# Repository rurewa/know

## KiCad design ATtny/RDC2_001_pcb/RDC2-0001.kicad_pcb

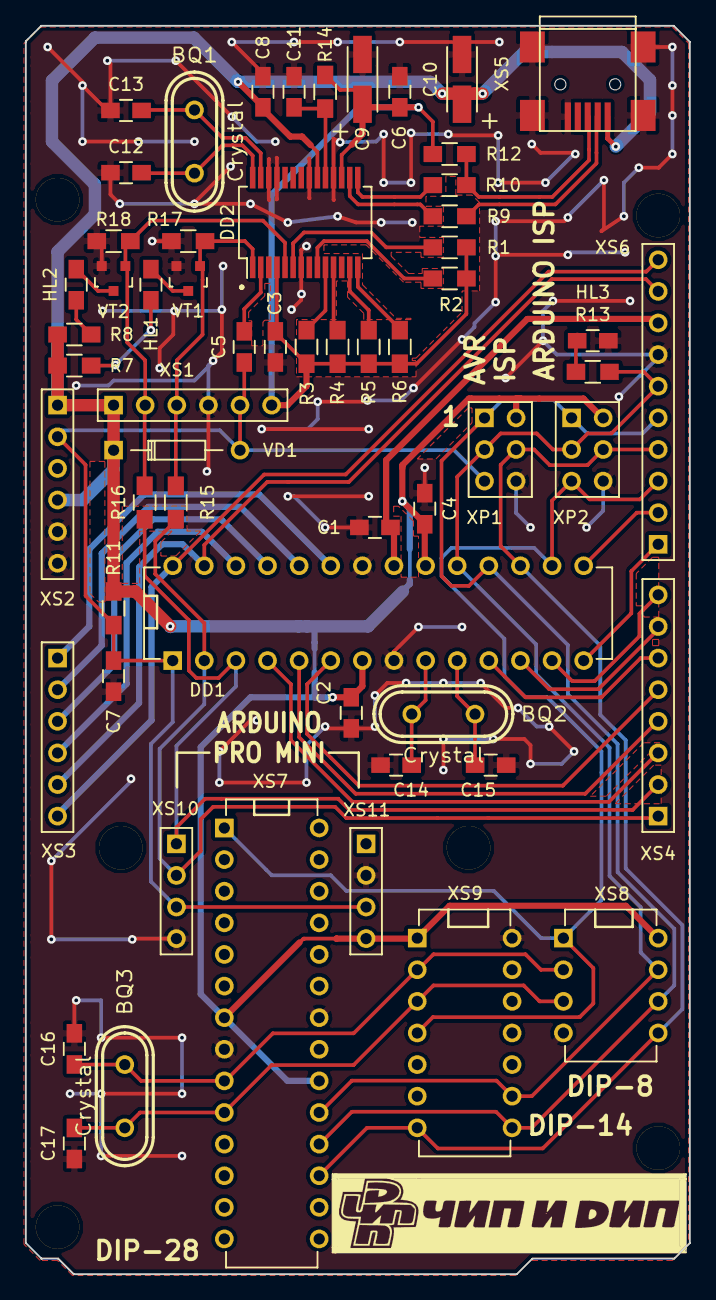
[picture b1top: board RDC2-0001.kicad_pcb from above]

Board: 2 copper layers, 53.3 x 100.3 mm, 59 parts (0 on the bottom side), 50 nets.

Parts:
BQ1, BQ2, BQ3: Crystal; CRYST_hc-49u_mm
C1, C2, C3, C4, C5, C6, C7, C8, C11, C12, C13, C14, C15, C16, C17: C; C_0805_HandSoldering
C9, C10: CP; TantalC_SizeA_EIA-3216_HandSoldering_mm
DD1: ATMEGA328P-P; DIP-28_W7.62mm_0.9x1.5
DD2: PL2303TA; SSOP-28_5.3x10.2mm_Pitch0.65mm
HL1, HL2, HL3: LED; C_0805_HandSoldering
R1, R2, R3, R4, R5, R6, R7, R8, R9, R10, R11, R12, R13, R14, R15, R16, R17, R18: R; R_0805_HandSoldering
VD1: D; Diode_DO-35_SOD27_Horizontal_RM10_mm
VT1, VT2: BSS138; SOT-23_mm
XP1, XP2: CONN_02X03; Pin_Header_Straight_2x03_mm
XS1, XS2, XS3: CONN_01X06; Pin_Header_Straight_1x06_mm
XS4: CONN_01X08; Pin_Header_Straight_1x08_mm
XS5: USB_OTG; USB_Mini-B_mm
XS6: CONN_01X10; Pin_Header_Straight_1x10_mm
XS7: ATMEGA328P-P; DIP-28_W7.62mm_0.9x1.5
XS8: ATTINY13A-P; DIP-8_W7.62mm_0.9x1.5
XS9: ATTINY24A-P; DIP-14_W7.62mm_0.9x1.5
XS10, XS11: CONN_01X04; Pin_Header_Straight_1x04_mm

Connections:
3V3: C3.2, C6.1, C9.1, DD2.4, DD2.17, R1.1, R2.1, R3.1, R4.1, R5.1, R6.1, R12.2, R14.2, XS1.6
5V: C2.1, C4.1, C8.1, C10.1, DD1.7, DD1.20, DD2.20, R7.1, R8.1, R11.1, VD1.1, XP1.2, XP2.2, XS1.1, XS2.1, XS2.4, XS5.1, XS7.7, XS7.20, XS8.8, XS9.1, XS11.4
A0: DD1.23, XS3.1
A1: DD1.24, XS3.2
A2: DD1.25, XS3.3
A3: DD1.26, XS3.4
A4/SDA: DD1.27, XS3.5, XS6.9
A5/SCL: DD1.28, XS3.6, XS6.10
AREF: C1.1, DD1.21, XS6.8
D0: DD1.2, R15.1, XS4.1, XS10.2
D1: DD1.3, R16.1, XS4.2, XS10.1
D2: DD1.4, XS4.3
D3: DD1.5, XS4.4
D4: DD1.6, XS4.5
D5: DD1.11, XS4.6
D6: DD1.12, XS4.7
D7: DD1.13, XS4.8
D8: DD1.14, XS6.1
D9: DD1.15, XS6.2
D10/SS: DD1.16, XP2.5, XS6.3, XS7.1, XS8.1, XS9.4
D11/MOSI: DD1.17, XP1.4, XP2.4, XS6.4, XS7.17, XS8.5, XS9.7
D12/MISO: DD1.18, XP1.1, XP2.1, XS6.5, XS7.18, XS8.6, XS9.8
D13/SCK: DD1.19, R13.1, XP1.3, XP2.3, XS6.6, XS7.19, XS8.7, XS9.9
GND: C1.2, C2.2, C3.1, C4.2, C6.2, C7.2, C8.2, C9.2, C10.2, C11.2, C12.1, C13.1, C14.1, C15.1, C16.1, C17.1, DD1.8, DD1.22, DD2.7, DD2.18, DD2.21, DD2.25, DD2.26, HL3.1, R17.2, R18.2, VT1.2, VT2.2, XP1.6, XP2.6, XS1.4, XS2.5, XS2.6, XS5.5, XS5.6, XS6.7, XS7.8, XS7.22, XS8.4, XS9.14, XS10.4, XS11.2
unnamed: BQ1.1, C12.2, DD2.28
unnamed: BQ1.2, C13.2, DD2.27
unnamed: BQ2.1, C14.2, DD1.9
unnamed: BQ2.2, C15.2, DD1.10
unnamed: C5.1, DD2.2
unnamed: C11.1, DD2.19, R14.1
unnamed: DD2.6, R1.2
unnamed: DD2.9, R2.2
unnamed: DD2.10, R3.2
unnamed: DD2.11, R4.2
unnamed: DD2.13, R5.2
unnamed: DD2.14, R6.2
unnamed: DD2.15, R10.1
unnamed: DD2.16, R9.1
unnamed: HL1.1, VT1.3
unnamed: HL1.2, R7.2
unnamed: HL2.1, VT2.3
unnamed: HL2.2, R8.2
unnamed: HL3.2, R13.2
unnamed: R9.2, XS5.2
unnamed: R10.2, R12.1, XS5.3
RES: C5.2, C7.1, DD1.1, R11.2, VD1.2, XP1.5, XS1.5, XS2.2, XS10.3, XS11.3
RXD: DD2.5, R16.2, R18.1, VT2.1, XS1.2
TXD: DD2.1, R15.2, R17.1, VT1.1, XS1.3
XTAL1: BQ3.1, C16.2, XS7.9, XS8.2, XS9.2
XTAL2: BQ3.2, C17.2, XS7.10, XS8.3, XS9.3

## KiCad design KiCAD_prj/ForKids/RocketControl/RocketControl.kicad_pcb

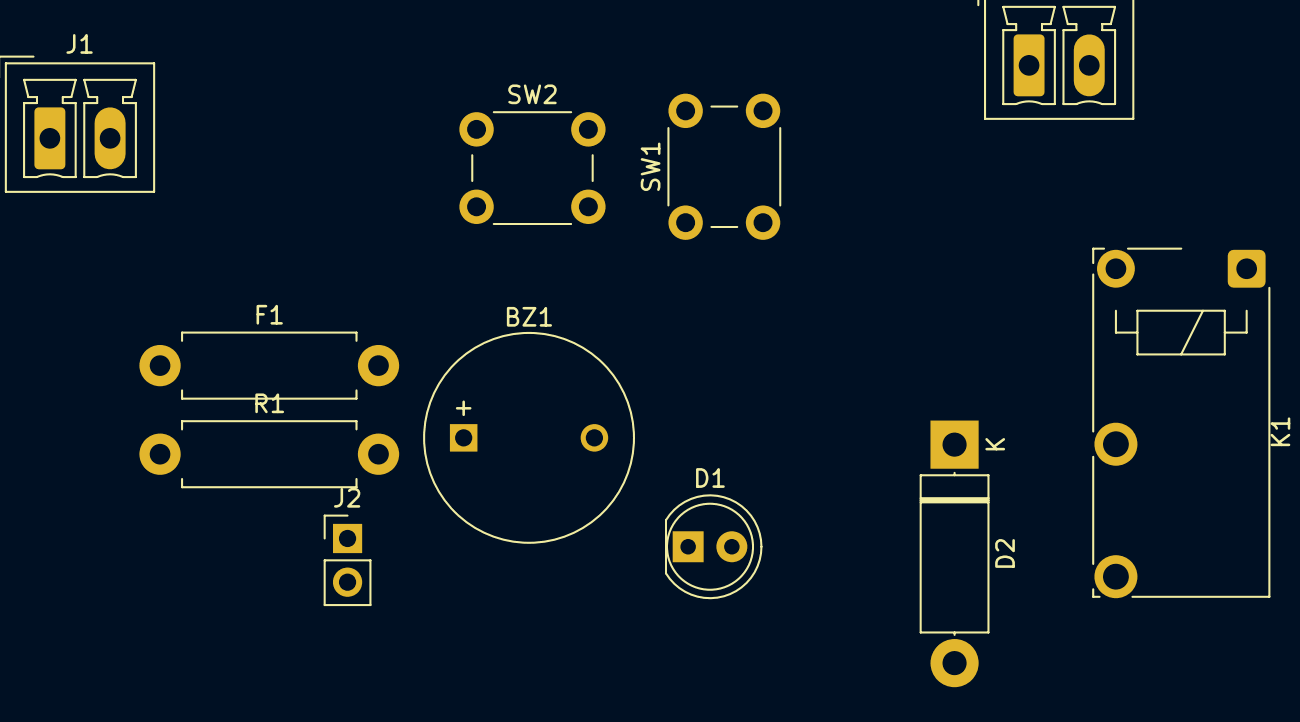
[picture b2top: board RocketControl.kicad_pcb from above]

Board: 2 copper layers, 11 parts (0 on the bottom side), 7 nets, no tracks yet.

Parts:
BZ1: Buzzer; MagneticBuzzer_ProSignal_ABI-010-RC
D1: LED; LED_D5.0mm
D2: DIODE; D_5W_P12.70mm_Horizontal
F1: 5A; R_Axial_DIN0411_L9.9mm_D3.6mm_P12.70mm_Horizontal
J1: Conn_01x02_Female; PhoenixContact_MCV_1,5_2-G-3.5_1x02_P3.50mm_Vertical
J2: Screw_Terminal_01x02; PinHeader_1x02_P2.54mm_Vertical
K1: DIPxx-1Axx-11x; Relay_SPST_TE_PCH-1xxx2M
L1: L; PhoenixContact_MCV_1,5_2-G-3.5_1x02_P3.50mm_Vertical
R1: 10K; R_Axial_DIN0411_L9.9mm_D3.6mm_P12.70mm_Horizontal
SW1, SW2: SW_MEC_5G; SW_PUSH_6mm

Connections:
+12V: J1.1, J2.1, SW2.1, SW2.2
Earth: F1.2, J2.2
unnamed: BZ1.1, D1.2
unnamed: BZ1.2, D2.1, F1.1, K1.2, L1.2, R1.1
unnamed: D1.1, R1.2
unnamed: J1.2, SW1.1, SW1.2
unnamed: K1.1, L1.1

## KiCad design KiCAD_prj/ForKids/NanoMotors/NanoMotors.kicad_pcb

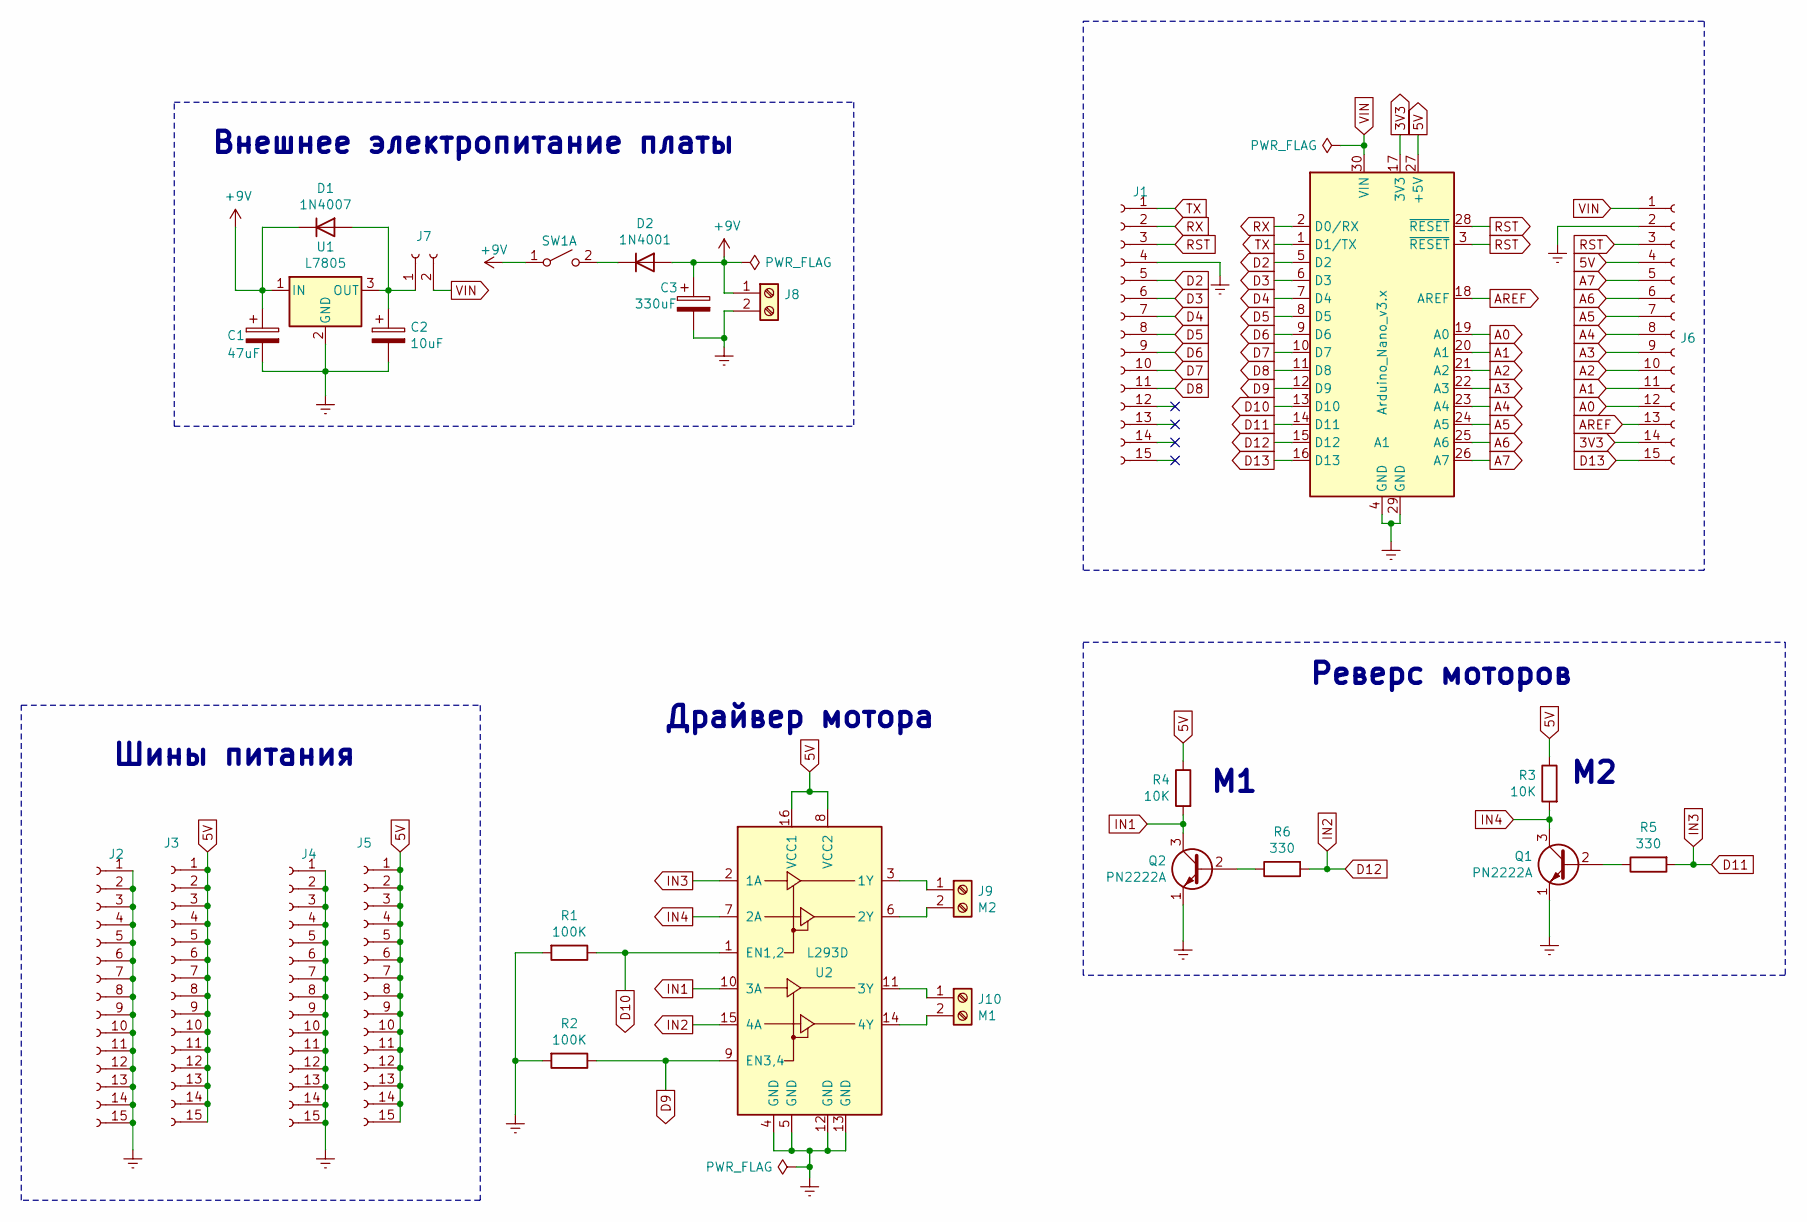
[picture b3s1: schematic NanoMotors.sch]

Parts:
A1: Arduino_Nano_v3.x; Arduino_Nano
C1: 47uF; CP_Radial_D6.3mm_P2.50mm
C2: 10uF; CP_Radial_D6.3mm_P2.50mm
C3: 330uF; CP_Radial_D6.3mm_P2.50mm
D1: 1N4007; D_DO-41_SOD81_P10.16mm_Horizontal
D2: 1N4001; D_DO-41_SOD81_P10.16mm_Horizontal
J1, J2, J3, J4, J5, J6: Conn_01x15_Female; PinHeader_1x15_P2.54mm_Vertical
J7: Conn_01x02_Female; PinHeader_1x02_P2.54mm_Vertical
J8: Screw_Terminal_01x02; PhoenixContact_MCV_1,5_2-G-3.5_1x02_P3.50mm_Vertical
J9: M2; PhoenixContact_MCV_1,5_2-G-3.5_1x02_P3.50mm_Vertical
J10: M1; PhoenixContact_MCV_1,5_2-G-3.5_1x02_P3.50mm_Vertical
Q1, Q2: PN2222A; TO-92_Inline_Wide
R1, R2: 100K; R_Axial_DIN0309_L9.0mm_D3.2mm_P12.70mm_Horizontal
R3, R4: 10K; R_Axial_DIN0309_L9.0mm_D3.2mm_P12.70mm_Horizontal
R5, R6: 330; R_Axial_DIN0309_L9.0mm_D3.2mm_P12.70mm_Horizontal
SW1: SW_DPST_x2; PinHeader_1x03_P2.54mm_Vertical
U1: L7805; TO-252-3_TabPin2
U2: L293D; DIP-16_W7.62mm

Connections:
3V3: A1.17 (3V3), J6.14
5V: A1.27 (+5V), J3.1, J3.2, J3.3, J3.4, J3.5, J3.6, J3.7, J3.8, J3.9, J3.10, J3.11, J3.12, J3.13, J3.14, J3.15, J5.1, J5.2, J5.3, J5.4, J5.5, J5.6, J5.7, J5.8, J5.9, J5.10, J5.11, J5.12, J5.13, J5.14, J5.15, J6.4, R3.1, R4.1, U2.8 (VCC2), U2.16 (VCC1)
+9V: C1.1, C3.1, D1.1 (K), D2.2 (A), J8.1, SW1.1 (A), U1.1 (IN)
A0: A1.19 (A0), J6.12
A1: A1.20 (A1), J6.11
A2: A1.21 (A2), J6.10
A3: A1.22 (A3), J6.9
A4: A1.23 (A4), J6.8
A5: A1.24 (A5), J6.7
A6: A1.25 (A6), J6.6
A7: A1.26 (A7), J6.5
AREF: A1.18 (AREF), J6.13
D2: A1.5 (D2), J1.5
D3: A1.6 (D3), J1.6
D4: A1.7 (D4), J1.7
D5: A1.8 (D5), J1.8
D6: A1.9 (D6), J1.9
D7: A1.10 (D7), J1.10
D8: A1.11 (D8), J1.11
D9: A1.12 (D9), R2.1, U2.9 (EN3,4)
D10: A1.13 (D10), R1.1, U2.1 (EN1,2)
D11: A1.14 (D11), R5.2, U2.2 (1A)
D12: A1.15 (D12), R6.2, U2.15 (4A)
D13: A1.16 (D13), J6.15
Earth: A1.4 (GND), A1.29 (GND), C1.2, C2.2, C3.2, J1.4, J2.1, J2.2, J2.3, J2.4, J2.5, J2.6, J2.7, J2.8, J2.9, J2.10, J2.11, J2.12, J2.13, J2.14, J2.15, J4.1, J4.2, J4.3, J4.4, J4.5, J4.6, J4.7, J4.8, J4.9, J4.10, J4.11, J4.12, J4.13, J4.14, J4.15, J6.2, J8.2, Q1.1 (E), Q2.1 (E), R1.2, R2.2, U1.2 (GND), U2.4 (GND), U2.5 (GND), U2.12 (GND), U2.13 (GND)
IN1: Q2.3 (C), R4.2, U2.10 (3A)
IN4: Q1.3 (C), R3.2, U2.7 (2A)
unnamed: C2.1, D1.2 (A), J7.1, U1.3 (OUT)
unnamed: D2.1 (K), SW1.2 (B)
unnamed: J9.1, U2.3 (1Y)
unnamed: J9.2, U2.6 (2Y)
unnamed: J10.1, U2.11 (3Y)
unnamed: J10.2, U2.14 (4Y)
unnamed: Q1.2 (B), R5.1
unnamed: Q2.2 (B), R6.1
RST: A1.3 (~RESET), A1.28 (~RESET), J1.3, J6.3
RX: A1.2 (D0/RX), J1.2
TX: A1.1 (D1/TX), J1.1
VIN: A1.30 (VIN), J6.1, J7.2

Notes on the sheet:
Шины питания
Внешнее электропитание платы
Реверс моторов
Драйвер мотора

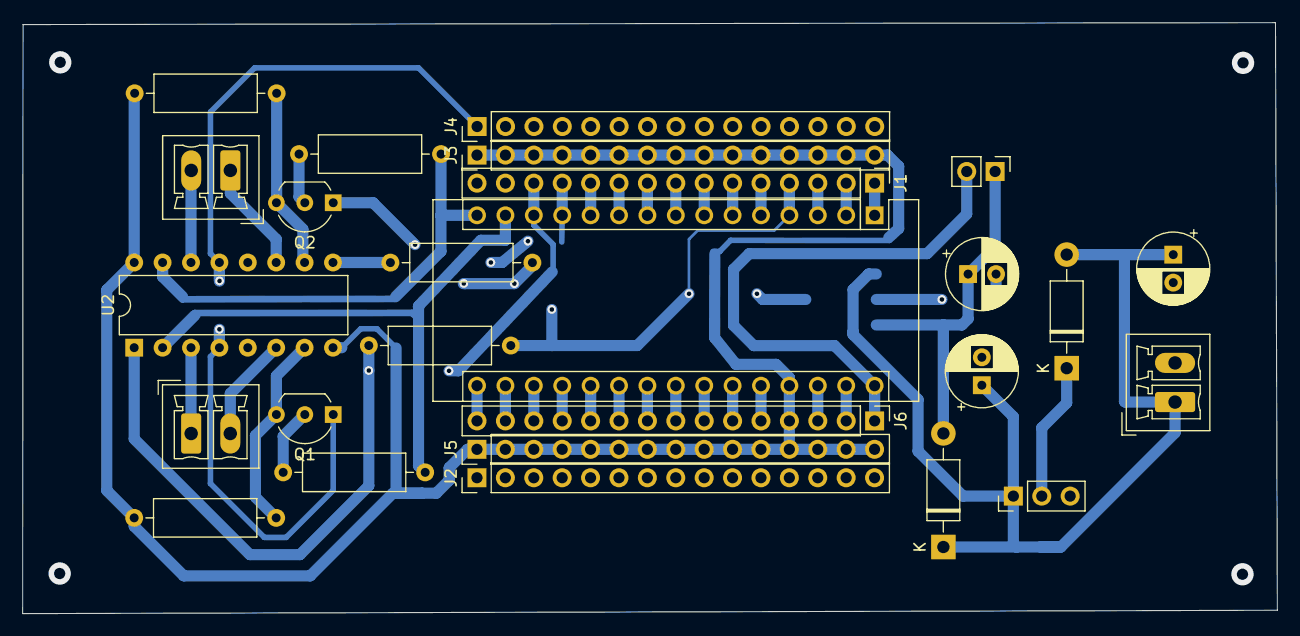
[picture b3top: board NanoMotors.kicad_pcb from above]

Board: 2 copper layers, 112.2 x 52.9 mm, 27 parts (1 on the bottom side), 39 nets.

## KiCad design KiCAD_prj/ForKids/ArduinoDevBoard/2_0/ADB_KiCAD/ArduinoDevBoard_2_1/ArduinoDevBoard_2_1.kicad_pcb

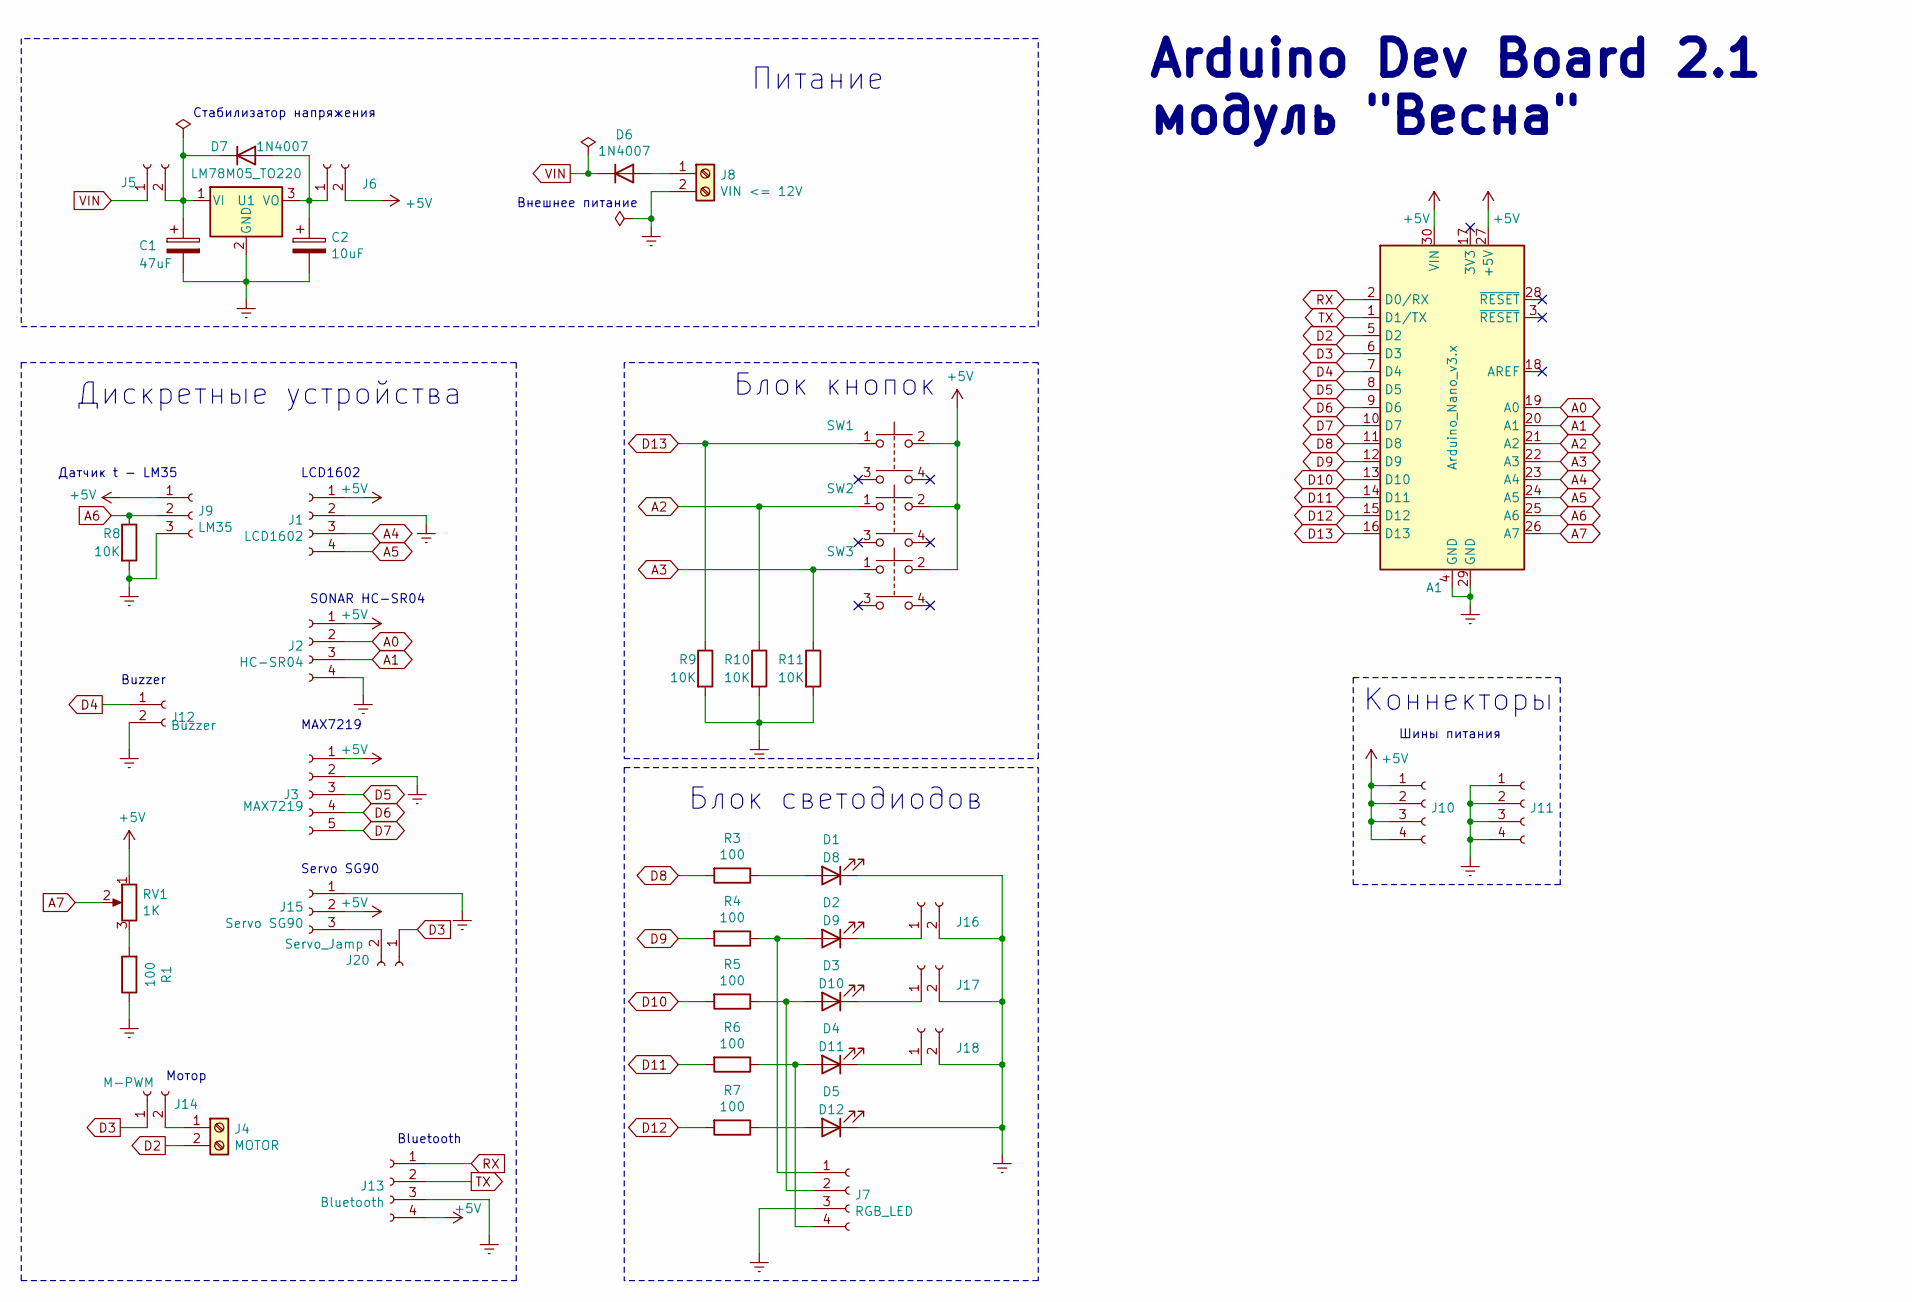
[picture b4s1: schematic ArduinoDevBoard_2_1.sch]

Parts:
A1: Arduino_Nano_v3.x; Arduino_Nano
C1: 47uF; CP_Radial_D5.0mm_P2.50mm
C2: 10uF; CP_Radial_D5.0mm_P2.50mm
D1: D8; LED_D5.0mm
D2: D9; LED_D5.0mm
D3: D10; LED_D5.0mm
D4: D11; LED_D5.0mm
D5: D12; LED_D5.0mm
D6, D7: 1N4007; D_A-405_P7.62mm_Horizontal
J1: LCD1602; PinHeader_1x04_P2.54mm_Vertical
J2: HC-SR04; PinSocket_1x04_P2.54mm_Vertical
J3: MAX7219; PinHeader_1x05_P2.54mm_Vertical
J4: MOTOR; PinHeader_1x02_P2.54mm_Vertical
J5: VIN_JAMP_1; PinHeader_1x02_P2.54mm_Vertical
J6: VIN_JAMP_2; PinHeader_1x02_P2.54mm_Vertical
J7: RGB_LED; PinHeader_1x04_P2.54mm_Vertical
J8: VIN <= 12V; PhoenixContact_MCV_1,5_2-G-3.5_1x02_P3.50mm_Vertical
J9: LM35; PinSocket_1x03_P2.54mm_Vertical
J10: +5V; PinHeader_1x04_P2.54mm_Vertical
J11: GND; PinHeader_1x04_P2.54mm_Vertical
J12: Buzzer; PinHeader_1x02_P2.54mm_Vertical
J13: Bluetooth; PinHeader_1x04_P2.54mm_Vertical
J14: M-PWM; PinHeader_1x02_P2.54mm_Vertical
J15: Servo SG90; PinSocket_1x03_P2.54mm_Vertical
J16: D9; PinHeader_1x02_P2.54mm_Vertical
J17: D10; PinHeader_1x02_P2.54mm_Vertical
J18: D11; PinHeader_1x02_P2.54mm_Vertical
J20: Servo_Jamp; PinHeader_1x02_P2.54mm_Vertical
R1, R3, R4, R5, R6, R7: 100; R_Axial_DIN0411_L9.9mm_D3.6mm_P12.70mm_Horizontal
R8, R9, R10, R11: 10K; R_Axial_DIN0411_L9.9mm_D3.6mm_P12.70mm_Horizontal
RV1: 1K; Potentiometer_Runtron_RM-065_Vertical
SW1: D13; SW_PUSH_6mm
SW2: D16; SW_PUSH_6mm
SW3: D17; SW_PUSH_6mm
U1: LM78M05_TO220; TO-252-3_TabPin2

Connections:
+5V: A1.27 (+5V), A1.30 (VIN), J1.1, J2.1, J3.1, J6.2, J9.1, J10.1, J10.2, J10.3, J10.4, J13.4, J15.2, RV1.1, SW1.2, SW2.2, SW3.2
A0: A1.19 (A0), J2.2
A1: A1.20 (A1), J2.3
A2: A1.21 (A2), R10.1, SW2.1
A3: A1.22 (A3), R11.1, SW3.1
A4: A1.23 (A4), J1.3
A5: A1.24 (A5), J1.4
A6: A1.25 (A6), J9.2, R8.1
A7: A1.26 (A7), RV1.2
D2: A1.5 (D2), J4.2
D3: A1.6 (D3), J14.1, J20.1
D4: A1.7 (D4), J12.1
D5: A1.8 (D5), J3.3
D6: A1.9 (D6), J3.4
D7: A1.10 (D7), J3.5
D8: A1.11 (D8), R3.2
D9: A1.12 (D9), R4.2
D10: A1.13 (D10), R5.2
D11: A1.14 (D11), R6.2
D12: A1.15 (D12), R7.2
D13: A1.16 (D13), R9.1, SW1.1
Earth: A1.4 (GND), A1.29 (GND), C1.2, C2.2, D1.1 (K), D5.1 (K), J1.2, J2.4, J3.2, J7.3, J8.2, J9.3, J11.1, J11.2, J11.3, J11.4, J12.2, J13.3, J15.1, J16.2, J17.2, J18.2, R1.1, R8.2, R9.2, R10.2, R11.2, U1.2 (GND)
unnamed: C1.1, D7.1 (K), J5.2, U1.1 (VI)
unnamed: C2.1, D7.2 (A), J6.1, U1.3 (VO)
unnamed: D1.2 (A), R3.1
unnamed: D2.1 (K), J16.1
unnamed: D2.2 (A), J7.1, R4.1
unnamed: D3.1 (K), J17.1
unnamed: D3.2 (A), J7.2, R5.1
unnamed: D4.1 (K), J18.1
unnamed: D4.2 (A), J7.4, R6.1
unnamed: D5.2 (A), R7.1
unnamed: D6.2 (A), J8.1
unnamed: J4.1, J14.2
unnamed: J15.3, J20.2
unnamed: R1.2, RV1.3
RX: A1.2 (D0/RX), J13.1
TX: A1.1 (D1/TX), J13.2
VIN: D6.1 (K), J5.1

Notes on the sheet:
Мотор
Стабилизатор напряжения
Датчик t - LM35
Внешнее питание
Блок кнопок
Блок светодиодов
Шины питания
Buzzer
MAX7219
SONAR HC-SR04
LCD1602
Servo SG90
Дискретные устройства
Коннекторы
Питание
Bluetooth
Arduino Dev Board 2.1 модуль "Весна"

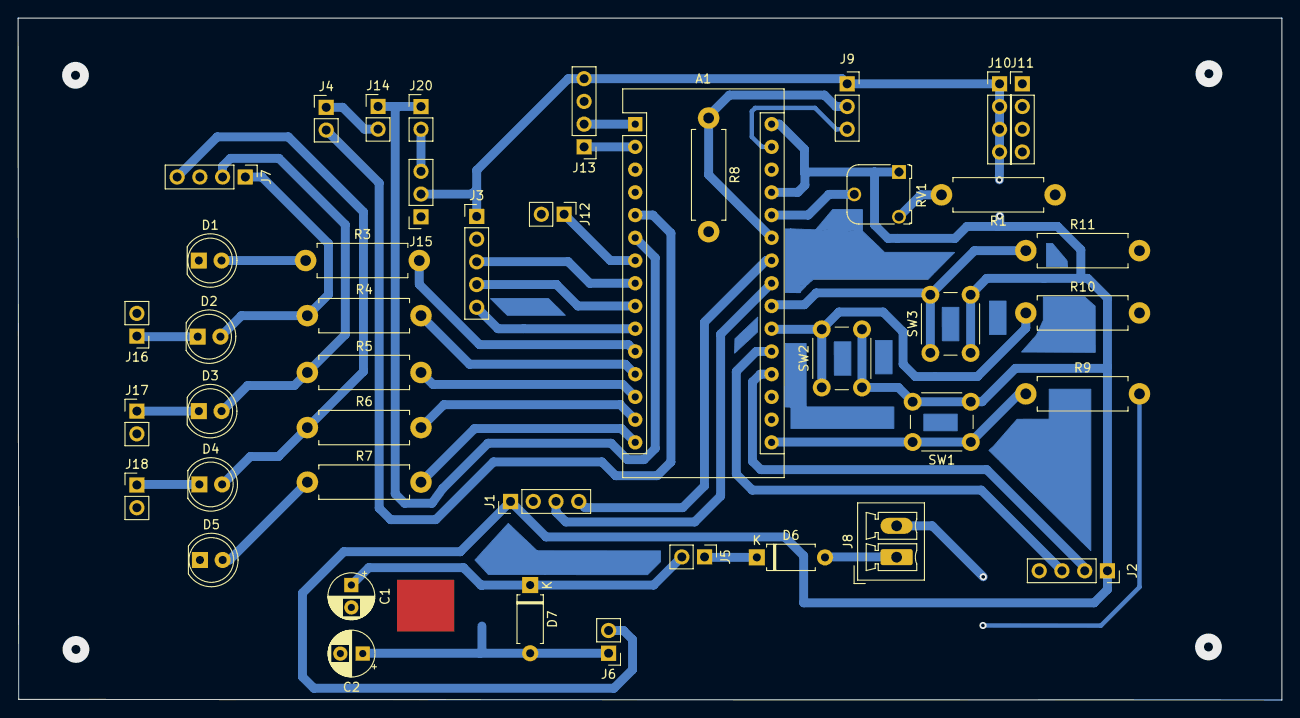
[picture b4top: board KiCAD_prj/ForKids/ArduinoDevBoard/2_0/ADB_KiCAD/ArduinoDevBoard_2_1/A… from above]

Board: 2 copper layers, 141.2 x 76.2 mm, 44 parts (1 on the bottom side), 39 nets.

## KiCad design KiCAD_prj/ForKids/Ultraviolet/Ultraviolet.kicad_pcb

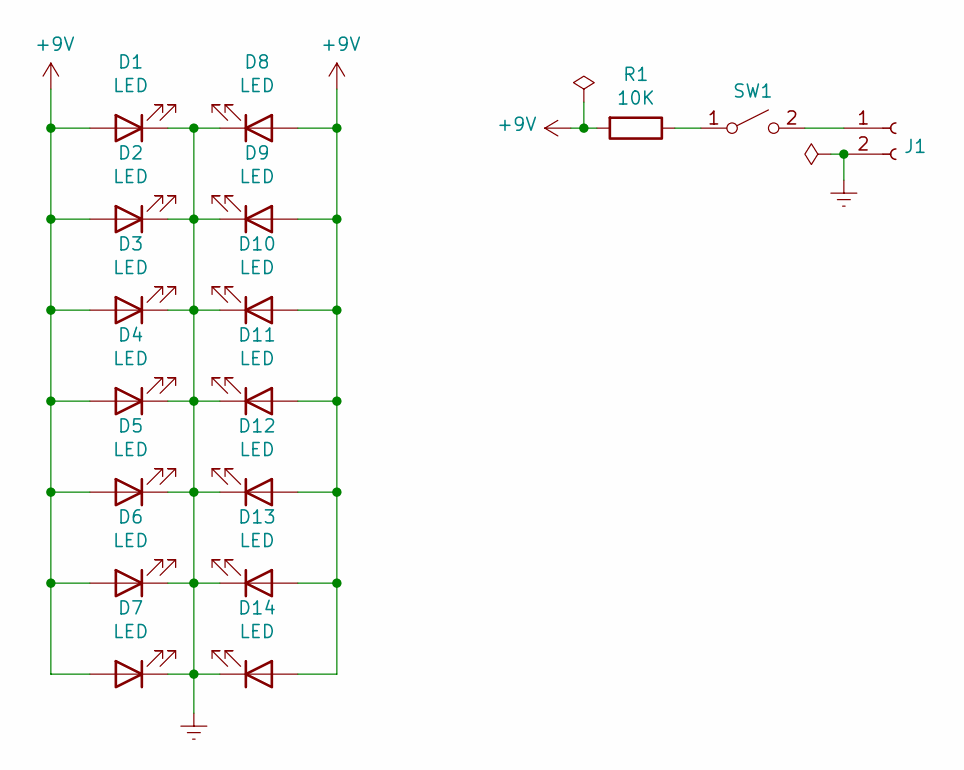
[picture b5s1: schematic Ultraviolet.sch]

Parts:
D1, D2, D3, D4, D5, D6, D7, D8, D9, D10, D11, D12, D13, D14: LED; LED_D5.0mm_Clear
J1: Conn_01x02_Female; PinHeader_1x02_P2.54mm_Vertical
R1: 10K; R_Axial_DIN0207_L6.3mm_D2.5mm_P10.16mm_Horizontal
SW1: SW_SPST; SW_CuK_OS102011MA1QN1_SPDT_Angled

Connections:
+9V: D1.2 (A), D2.2 (A), D3.2 (A), D4.2 (A), D5.2 (A), D6.2 (A), D7.2 (A), D8.2 (A), D9.2 (A), D10.2 (A), D11.2 (A), D12.2 (A), D13.2 (A), D14.2 (A), R1.2
Earth: D1.1 (K), D2.1 (K), D3.1 (K), D4.1 (K), D5.1 (K), D6.1 (K), D7.1 (K), D8.1 (K), D9.1 (K), D10.1 (K), D11.1 (K), D12.1 (K), D13.1 (K), D14.1 (K), J1.2
unnamed: J1.1, SW1.2 (B)
unnamed: R1.1, SW1.1 (A)

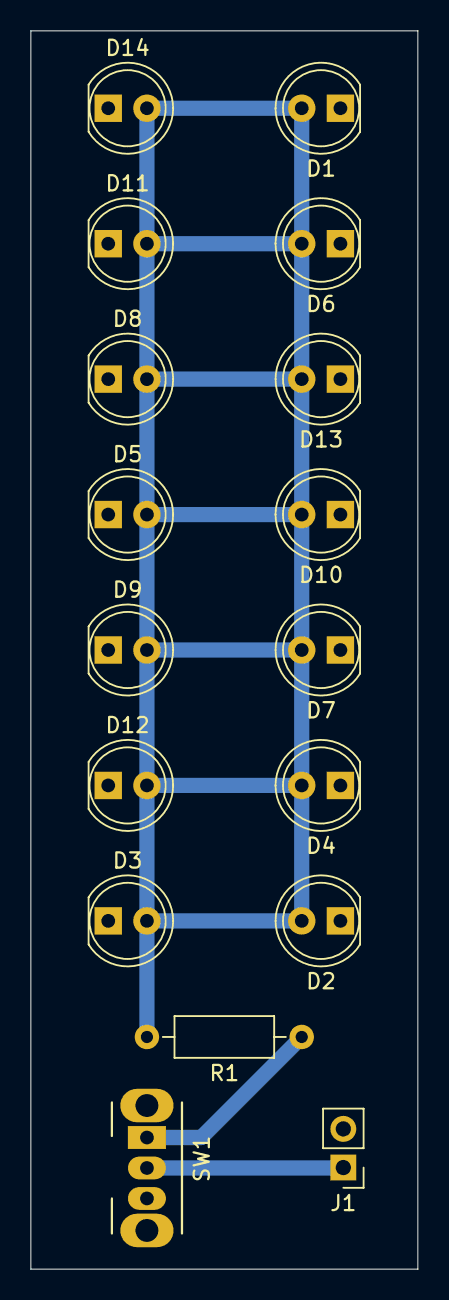
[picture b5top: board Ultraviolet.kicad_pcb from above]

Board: 2 copper layers, 25.4 x 81.3 mm, 17 parts (0 on the bottom side), 4 nets.

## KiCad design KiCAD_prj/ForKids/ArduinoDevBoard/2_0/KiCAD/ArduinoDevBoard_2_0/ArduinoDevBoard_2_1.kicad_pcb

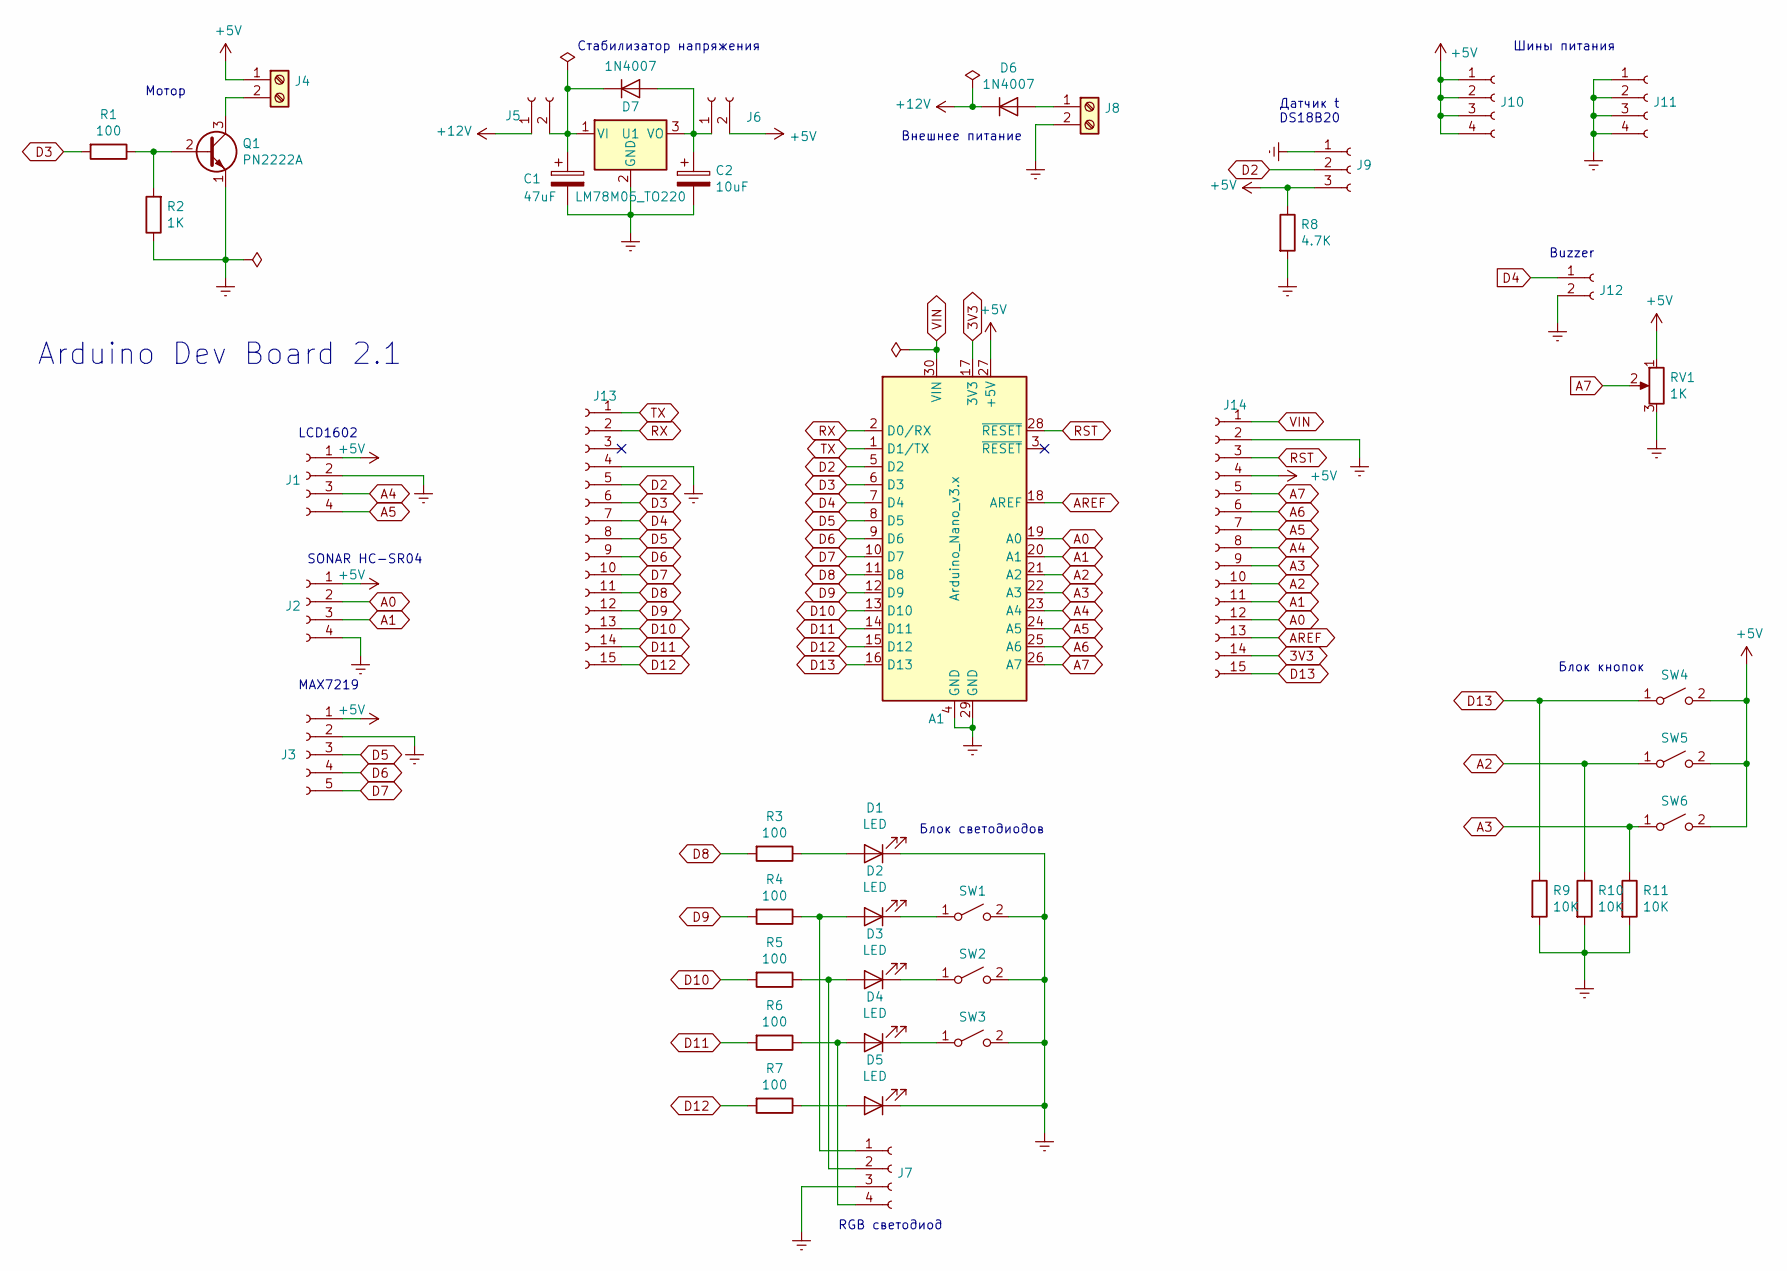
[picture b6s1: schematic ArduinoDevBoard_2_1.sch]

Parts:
A1: Arduino_Nano_v3.x; Arduino_Nano
C1: 47uF; CP_Radial_D5.0mm_P2.50mm
C2: 10uF; CP_Radial_D5.0mm_P2.50mm
D1, D2, D3, D4, D5: LED; LED_D5.0mm
D6, D7: 1N4007; D_A-405_P7.62mm_Horizontal
J1, J7, J10, J11: Conn_01x04_Female; PinHeader_1x04_P2.54mm_Vertical
J2: Conn_01x04_Female; PinSocket_1x04_P2.54mm_Vertical
J3: Conn_01x05_Female; PinHeader_1x05_P2.54mm_Vertical
J4, J8: Screw_Terminal_01x02; PhoenixContact_MCV_1,5_2-G-3.5_1x02_P3.50mm_Vertical
J5, J6, J12: Conn_01x02_Female; PinHeader_1x02_P2.54mm_Vertical
J9: Conn_01x03_Female; PinSocket_1x03_P2.54mm_Vertical
J13, J14: Conn_01x15_Female; PinSocket_1x15_P2.54mm_Vertical
Q1: PN2222A; TO-92_Inline_Wide
R1, R3, R4, R5, R6, R7: 100; R_Axial_DIN0411_L9.9mm_D3.6mm_P12.70mm_Horizontal
R2: 1K; R_Axial_DIN0411_L9.9mm_D3.6mm_P12.70mm_Horizontal
R8: 4.7K; R_Axial_DIN0411_L9.9mm_D3.6mm_P12.70mm_Horizontal
R9, R10, R11: 10K; R_Axial_DIN0411_L9.9mm_D3.6mm_P12.70mm_Horizontal
RV1: 1K; Potentiometer_Runtron_RM-065_Vertical
SW1, SW2, SW3: SW_SPST; PinHeader_1x02_P2.54mm_Vertical
SW4, SW5, SW6: SW_SPST; SW_PUSH_6mm_H5mm
U1: LM78M05_TO220; TO-92_Wide

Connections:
3V3: A1.17 (3V3), J14.14
+5V: A1.27 (+5V), J1.1, J2.1, J3.1, J4.1, J6.2, J9.3, J10.1, J10.2, J10.3, J10.4, J14.4, R8.1, RV1.1, SW4.2 (B), SW5.2 (B), SW6.2 (B)
+12V: D6.1 (K), J5.1
A0: A1.19 (A0), J2.2, J14.12
A1: A1.20 (A1), J2.3, J14.11
A2: A1.21 (A2), J14.10, R10.1, SW5.1 (A)
A3: A1.22 (A3), J14.9, R11.1, SW6.1 (A)
A4: A1.23 (A4), J1.3, J14.8
A5: A1.24 (A5), J1.4, J14.7
A6: A1.25 (A6), J14.6
A7: A1.26 (A7), J14.5, RV1.2
AREF: A1.18 (AREF), J14.13
D2: A1.5 (D2), J9.2, J13.5
D3: A1.6 (D3), J13.6, R1.2
D4: A1.7 (D4), J12.1, J13.7
D5: A1.8 (D5), J3.3, J13.8
D6: A1.9 (D6), J3.4, J13.9
D7: A1.10 (D7), J3.5, J13.10
D8: A1.11 (D8), J13.11, R3.2
D9: A1.12 (D9), J13.12, R4.2
D10: A1.13 (D10), J13.13, R5.2
D11: A1.14 (D11), J13.14, R6.2
D12: A1.15 (D12), J13.15, R7.2
D13: A1.16 (D13), J14.15, R9.1, SW4.1 (A)
Earth: A1.4 (GND), A1.29 (GND), C1.2, C2.2, D1.1 (K), D5.1 (K), J1.2, J2.4, J3.2, J7.3, J8.2, J9.1, J11.1, J11.2, J11.3, J11.4, J12.2, J13.4, J14.2, Q1.1 (E), R2.1, R8.2, R9.2, R10.2, R11.2, RV1.3, SW1.2 (B), SW2.2 (B), SW3.2 (B), U1.2 (GND)
unnamed: C1.1, D7.1 (K), J5.2, U1.1 (VI)
unnamed: C2.1, D7.2 (A), J6.1, U1.3 (VO)
unnamed: D1.2 (A), R3.1
unnamed: D2.1 (K), SW1.1 (A)
unnamed: D2.2 (A), J7.1, R4.1
unnamed: D3.1 (K), SW2.1 (A)
unnamed: D3.2 (A), J7.2, R5.1
unnamed: D4.1 (K), SW3.1 (A)
unnamed: D4.2 (A), J7.4, R6.1
unnamed: D5.2 (A), R7.1
unnamed: D6.2 (A), J8.1
unnamed: J4.2, Q1.3 (C)
unnamed: Q1.2 (B), R1.1, R2.2
RST: A1.28 (~RESET), J14.3
RX: A1.2 (D0/RX), J13.2
TX: A1.1 (D1/TX), J13.1
VIN: A1.30 (VIN), J14.1

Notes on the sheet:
Мотор
Стабилизатор напряжения
Датчик t DS18B20
Внешнее питание
Блок кнопок
Блок светодиодов
Шины питания
Buzzer
MAX7219
SONAR HC-SR04
LCD1602
Arduino Dev Board 2.1
RGB светодиод

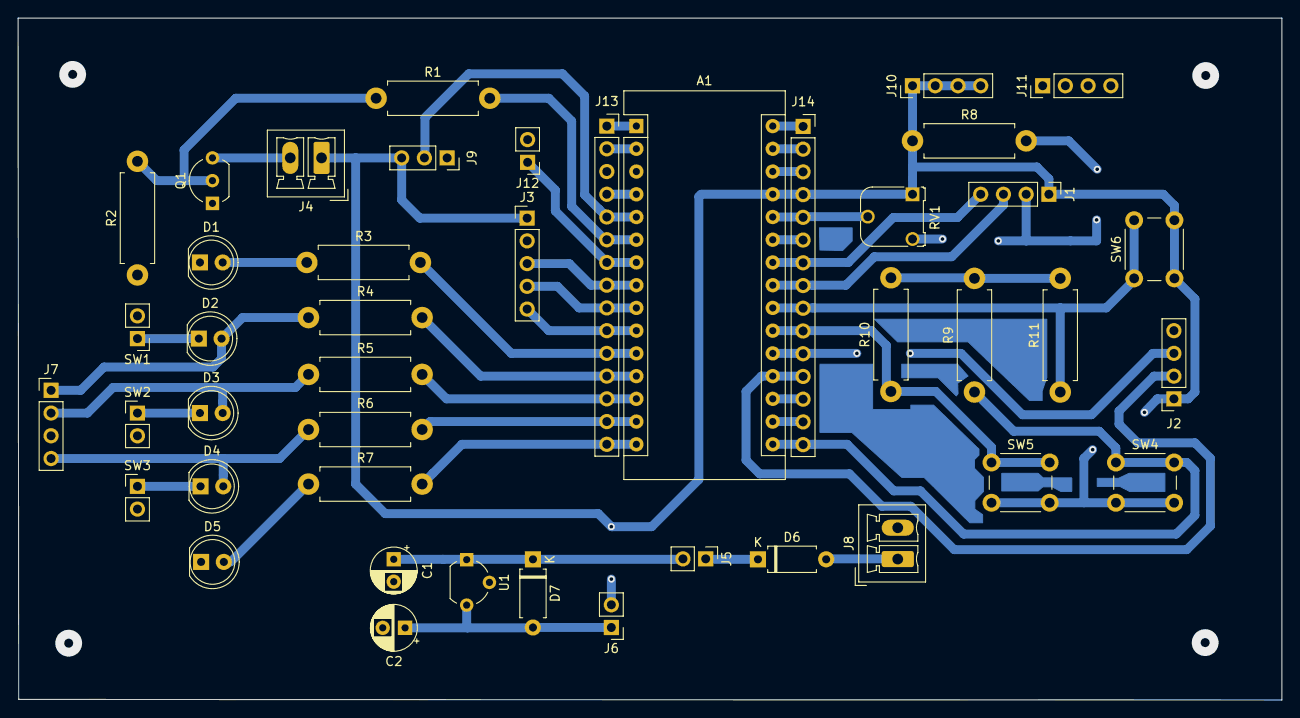
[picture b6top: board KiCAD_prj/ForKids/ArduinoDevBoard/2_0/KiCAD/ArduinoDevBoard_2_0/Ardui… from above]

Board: 2 copper layers, 141.2 x 76.2 mm, 44 parts (0 on the bottom side), 42 nets.

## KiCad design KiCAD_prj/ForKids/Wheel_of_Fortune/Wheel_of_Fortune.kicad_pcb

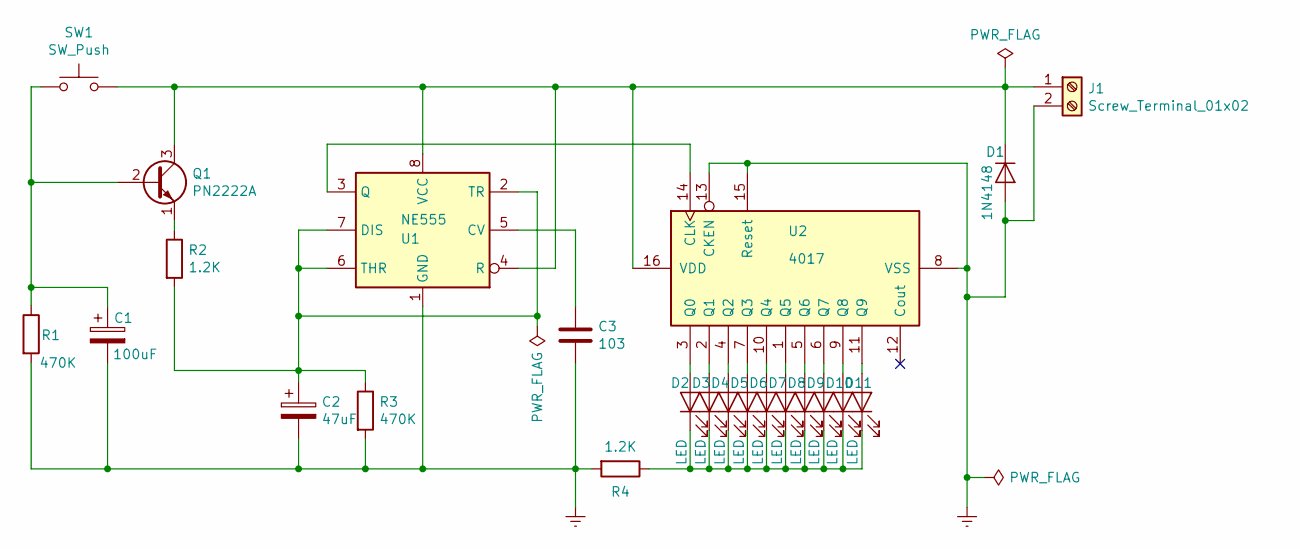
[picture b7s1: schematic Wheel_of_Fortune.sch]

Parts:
C1: 100uF; CP_Radial_D8.0mm_P3.80mm
C2: 47uF; CP_Radial_D8.0mm_P3.50mm
C3: 103; C_Disc_D7.5mm_W5.0mm_P7.50mm
D1: 1N4148; D_DO-35_SOD27_P7.62mm_Horizontal
D2, D3, D4, D5, D6, D7, D8, D9, D10, D11: LED; LED_D3.0mm
J1: Screw_Terminal_01x02; PhoenixContact_MCV_1,5_2-G-3.5_1x02_P3.50mm_Vertical
Q1: PN2222A; TO-92_Wide
R1, R3: 470K; R_Axial_DIN0207_L6.3mm_D2.5mm_P7.62mm_Horizontal
R2, R4: 1.2K; R_Axial_DIN0207_L6.3mm_D2.5mm_P7.62mm_Horizontal
SW1: SW_Push; SW_PUSH_6mm
U1: NE555; DIP-8_W7.62mm_LongPads
U2: 4017; DIP-16_W7.62mm_LongPads

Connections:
Earth: C1.2, C2.2, C3.2, D1.2 (A), J1.2, R1.2, R3.2, R4.2, U1.1 (GND), U2.8 (VSS), U2.13 (CKEN), U2.15 (Reset)
unnamed: C1.1, Q1.2 (B), R1.1, SW1.1
unnamed: C2.1, R2.2, R3.1
unnamed: C3.1, U1.5 (CV)
unnamed: D1.1 (K), J1.1, Q1.3 (C), SW1.2, U1.4 (R), U1.8 (VCC), U2.16 (VDD)
unnamed: D2.2 (A), U2.3 (Q0)
unnamed: D3.2 (A), U2.2 (Q1)
unnamed: D4.2 (A), U2.4 (Q2)
unnamed: D5.2 (A), U2.7 (Q3)
unnamed: D6.2 (A), U2.10 (Q4)
unnamed: D7.2 (A), U2.1 (Q5)
unnamed: D8.2 (A), U2.5 (Q6)
unnamed: D9.2 (A), U2.6 (Q7)
unnamed: D2.1 (K), D3.1 (K), D4.1 (K), D5.1 (K), D6.1 (K), D7.1 (K), D8.1 (K), D9.1 (K), D10.1 (K), D11.1 (K), R4.1
unnamed: D10.2 (A), U2.9 (Q8)
unnamed: D11.2 (A), U2.11 (Q9)
unnamed: Q1.1 (E), R2.1
unnamed: U1.2 (TR), U1.6 (THR), U1.7 (DIS)
unnamed: U1.3 (Q), U2.14 (CLK)
